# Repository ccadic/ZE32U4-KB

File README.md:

# ZE32U4-KB
12 low profile keys USB Keyboard with OLED, an ATMega32U4
Dr CADIC Philippe pcadic@gmail.com
GPL 3

This directory also has solidworks files for 3D files

The KAILH low profile are purchasable here: https://fr.aliexpress.com/item/32989908397.html?spm=a2g0s.9042311.0.0.27426c37iG4w2C
The Arduino like ATMEGA is a PRO MICRO : https://www.amazon.com/OSOYOO-ATmega32U4-arduino-Leonardo-ATmega328/dp/B012FOV17O/ref=pd_sbs_3/141-0280866-6867517
The OLED is an I2C SSD1336: https://www.amazon.com/Pieces-Display-Module-SSD1306-3-3V-5V/dp/B08CDN5PSJ/ref=sr_1_3?dchild=1&keywords=OLED+I2C&qid=1630262917&sr=8-3

Size: 70x80

You have a demo software for aduino in the appropriate subdirectory.

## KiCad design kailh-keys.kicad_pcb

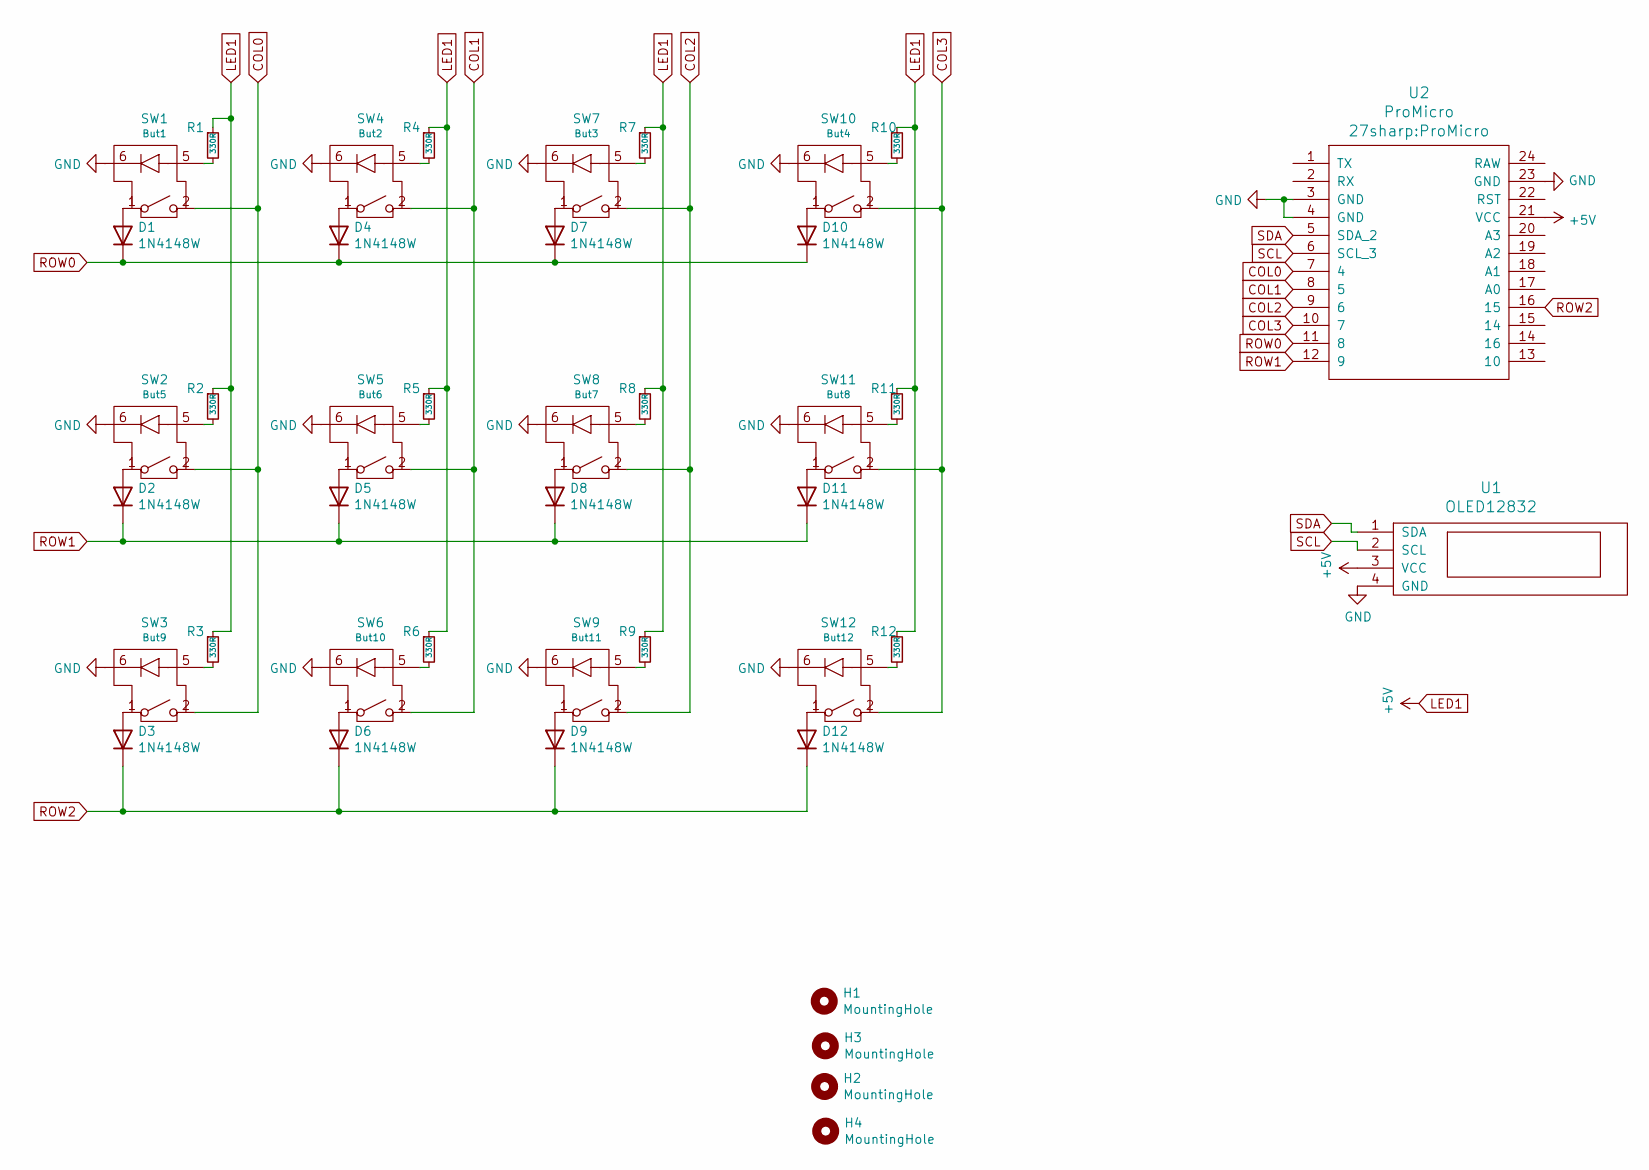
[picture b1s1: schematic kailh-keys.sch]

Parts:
D1, D2, D3, D4, D5, D6, D7, D8, D9, D10, D11, D12: 1N4148W; D_DO-35_SOD27_P7.62mm_Horizontal
H1, H2, H3, H4: MountingHole; MountingHole_2.5mm_Pad_Via
R1, R2, R3, R4, R5, R6, R7, R8, R9, R10, R11, R12: 330R; R_0603_1608Metric_Pad0.98x0.95mm_HandSolder
SW1: But1; KailhLP
SW2: But5; KailhLP
SW3: But9; KailhLP
SW4: But2; KailhLP
SW5: But6; KailhLP
SW6: But10; KailhLP
SW7: But3; KailhLP
SW8: But7; KailhLP
SW9: But11; KailhLP
SW10: But4; KailhLP
SW11: But8; KailhLP
SW12: But12; KailhLP
U1: OLED12832; OLED-0.91-128x32
U2: ProMicro

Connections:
COL0: SW1.2 (B), SW2.2 (B), SW3.2 (B), U2.7 (4)
COL1: SW4.2 (B), SW5.2 (B), SW6.2 (B), U2.8 (5)
COL2: SW7.2 (B), SW8.2 (B), SW9.2 (B), U2.9 (6)
COL3: SW10.2 (B), SW11.2 (B), SW12.2 (B), U2.10 (7)
GND: SW1.6 (Cath), SW2.6 (Cath), SW3.6 (Cath), SW4.6 (Cath), SW5.6 (Cath), SW6.6 (Cath), SW7.6 (Cath), SW8.6 (Cath), SW9.6 (Cath), SW10.6 (Cath), SW11.6 (Cath), SW12.6 (Cath), U1.4 (GND), U2.3 (GND), U2.4 (GND), U2.23 (GND)
LED1: R1.1, R2.1, R3.1, R4.1, R5.1, R6.1, R7.1, R8.1, R9.1, R10.1, R11.1, R12.1, U1.3 (VCC), U2.21 (VCC)
unnamed: D1.2 (A), SW1.1 (A)
unnamed: D2.2 (A), SW2.1 (A)
unnamed: D3.2 (A), SW3.1 (A)
unnamed: D4.2 (A), SW4.1 (A)
unnamed: D5.2 (A), SW5.1 (A)
unnamed: D6.2 (A), SW6.1 (A)
unnamed: D7.2 (A), SW7.1 (A)
unnamed: D8.2 (A), SW8.1 (A)
unnamed: D9.2 (A), SW9.1 (A)
unnamed: D10.2 (A), SW10.1 (A)
unnamed: D11.2 (A), SW11.1 (A)
unnamed: D12.2 (A), SW12.1 (A)
unnamed: R1.2, SW1.5 (Anod)
unnamed: R2.2, SW2.5 (Anod)
unnamed: R3.2, SW3.5 (Anod)
unnamed: R4.2, SW4.5 (Anod)
unnamed: R5.2, SW5.5 (Anod)
unnamed: R6.2, SW6.5 (Anod)
unnamed: R7.2, SW7.5 (Anod)
unnamed: R8.2, SW8.5 (Anod)
unnamed: R9.2, SW9.5 (Anod)
unnamed: R10.2, SW10.5 (Anod)
unnamed: R11.2, SW11.5 (Anod)
unnamed: R12.2, SW12.5 (Anod)
ROW0: D1.1 (K), D4.1 (K), D7.1 (K), D10.1 (K), U2.11 (8)
ROW1: D2.1 (K), D5.1 (K), D8.1 (K), D11.1 (K), U2.12 (9)
ROW2: D3.1 (K), D6.1 (K), D9.1 (K), D12.1 (K), U2.16 (15)
SCL: U1.2 (SCL), U2.6 (SCL_3)
SDA: U1.1 (SDA), U2.5 (SDA_2)

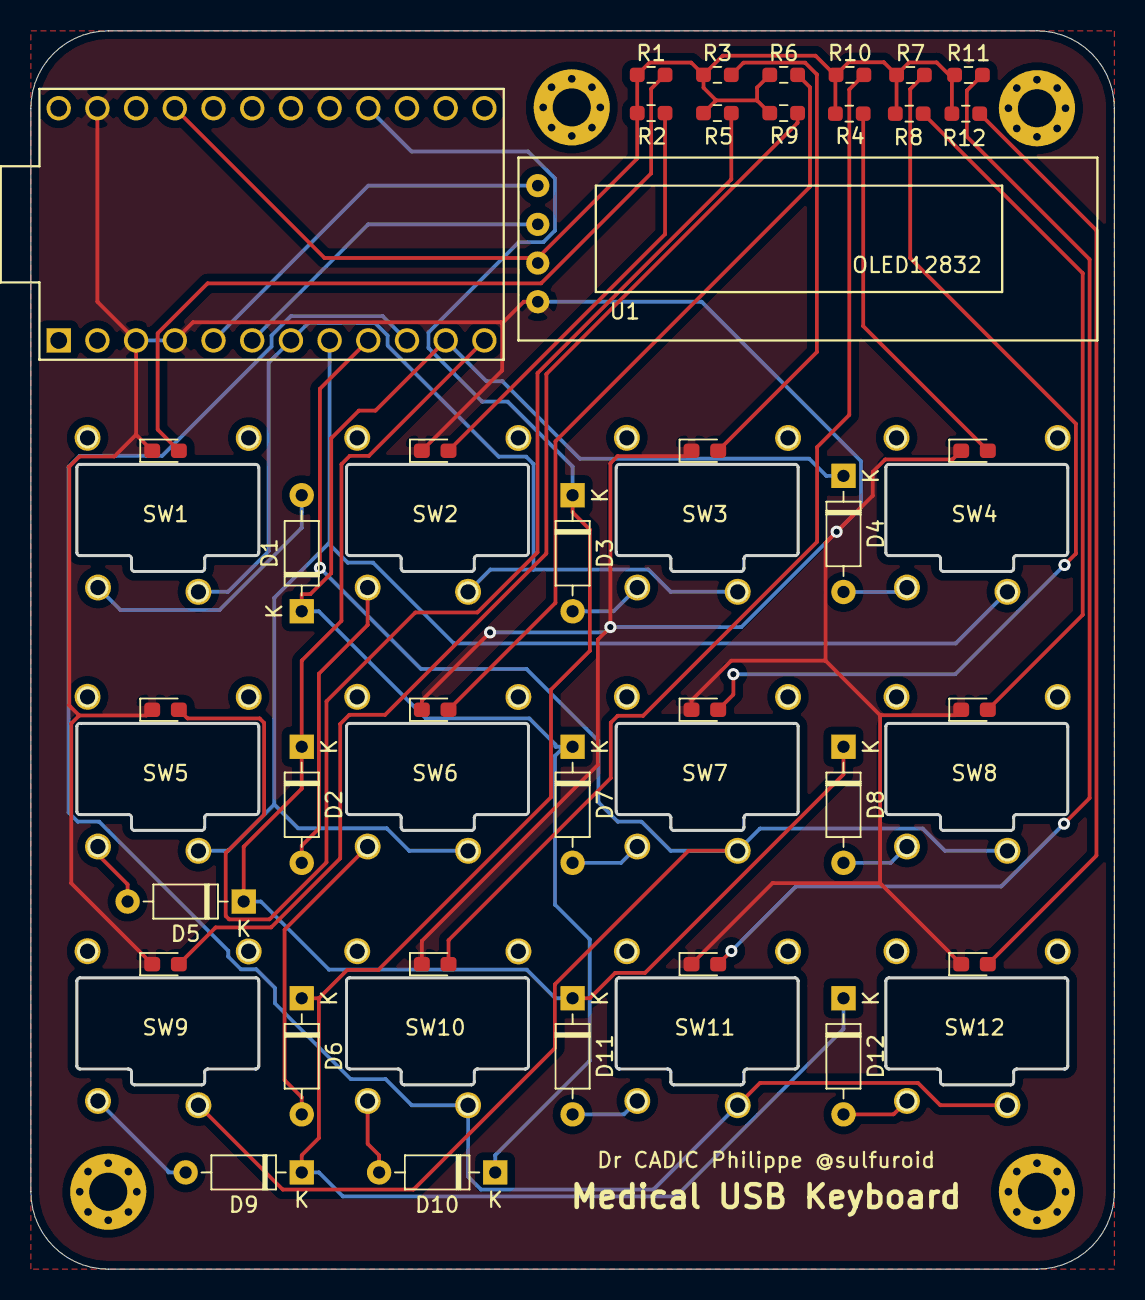
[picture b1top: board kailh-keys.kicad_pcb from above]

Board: 2 copper layers, 71.0 x 81.1 mm, 42 parts (0 on the bottom side), 35 nets.

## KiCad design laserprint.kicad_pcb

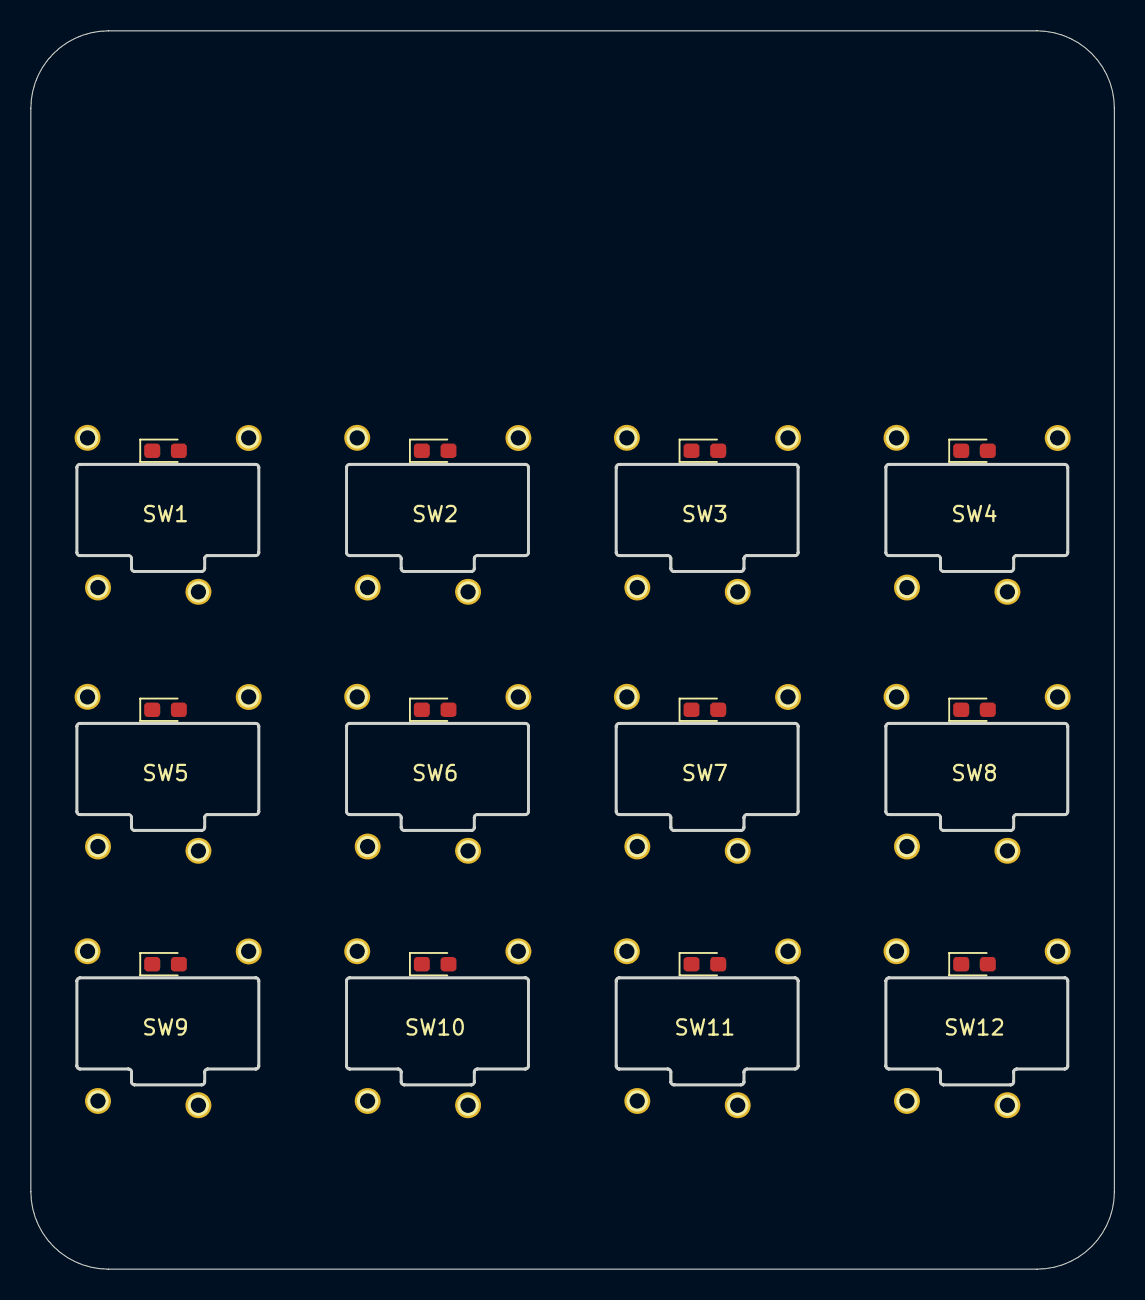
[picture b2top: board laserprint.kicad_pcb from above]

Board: 2 copper layers, 71.0 x 81.1 mm, 12 parts (0 on the bottom side), 5 nets, no tracks yet.

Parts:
SW1: But1; KailhLP
SW2: But5; KailhLP
SW3: But9; KailhLP
SW4: But2; KailhLP
SW5: But6; KailhLP
SW6: But10; KailhLP
SW7: But3; KailhLP
SW8: But7; KailhLP
SW9: But11; KailhLP
SW10: But4; KailhLP
SW11: But8; KailhLP
SW12: But12; KailhLP

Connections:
COL0: SW1.2, SW2.2, SW3.2
COL1: SW4.2, SW5.2, SW6.2
COL2: SW7.2, SW8.2, SW9.2
COL3: SW10.2, SW11.2, SW12.2
GND: SW1.6, SW2.6, SW3.6, SW4.6, SW5.6, SW6.6, SW7.6, SW8.6, SW9.6, SW10.6, SW11.6, SW12.6
